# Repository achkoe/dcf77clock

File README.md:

# dcf77clock

DCF77 clock with LED display using Raspberry Pi Pico.

## cc

Software for Raspberry Pi Pico.

## cad

Python files for generating SVG files for different parts
of the case for the clock.

## kicad

KiCAD layout data for clock hardware.

## simulator

Python script to simulate DCF77 sequence on Raspberry Pi.

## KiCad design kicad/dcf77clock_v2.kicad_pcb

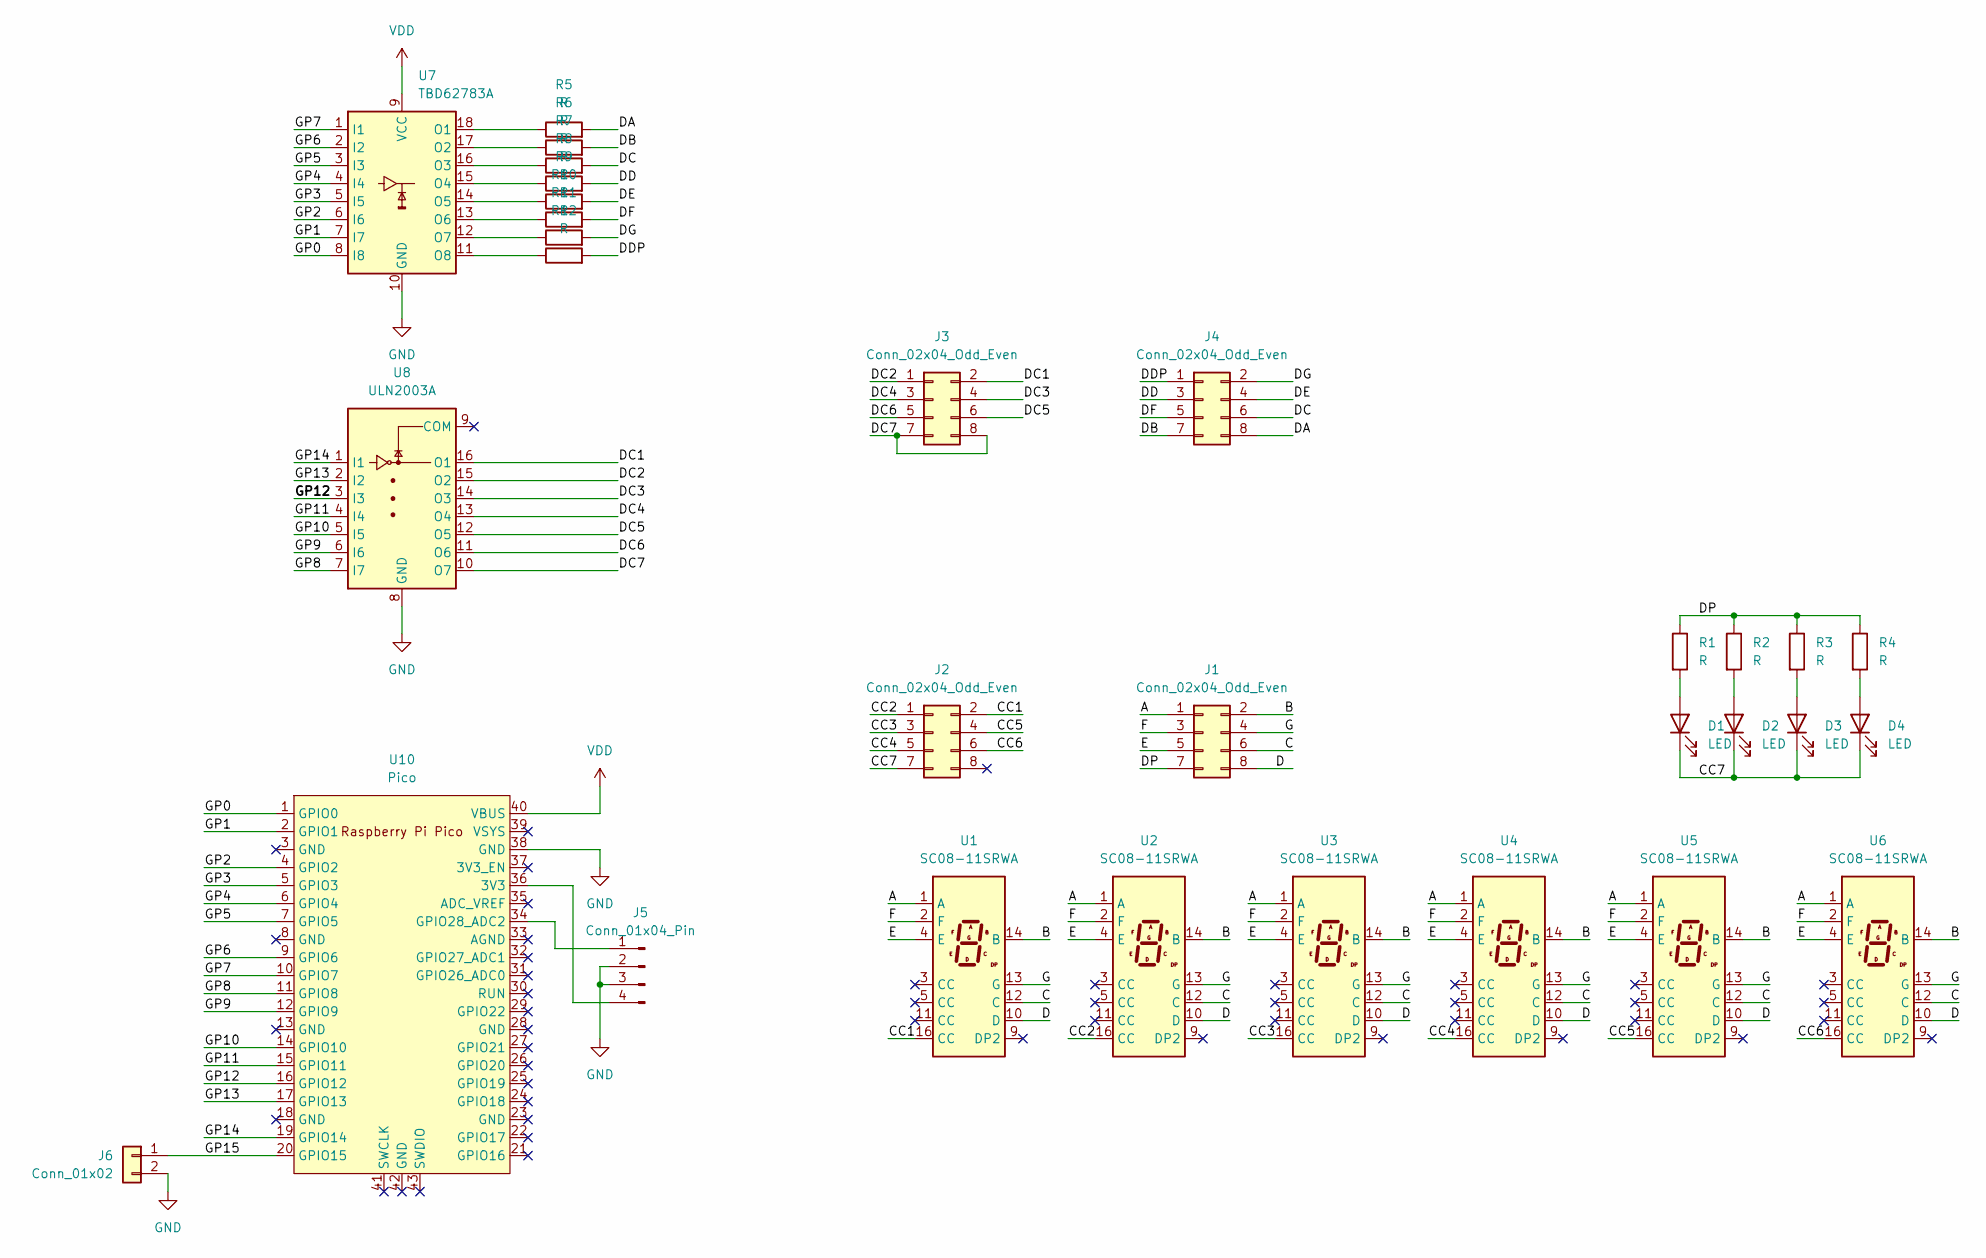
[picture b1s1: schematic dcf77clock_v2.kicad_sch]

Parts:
D1, D2, D3, D4: LED; LED_D3.0mm
J1, J2: Conn_02x04_Odd_Even; PinSocket_2x04_P2.54mm_Vertical
J3, J4: Conn_02x04_Odd_Even; PinHeader_2x04_P2.54mm_Vertical
J5: Conn_01x04_Pin; PinHeader_1x04_P2.54mm_Horizontal
J6: Conn_01x02; PinHeader_1x02_P2.54mm_Horizontal
R1, R2, R3, R4, R5, R6, R7, R8, R9, R10, R11, R12: R; R_Axial_DIN0207_L6.3mm_D2.5mm_P10.16mm_Horizontal
U1, U2, U3, U4, U5, U6: SC08-11SRWA; SC08-11SWRA
U7: TBD62783A; DIP-18_W7.62mm_LongPads
U8: ULN2003A; DIP-16_W7.62mm_LongPads
U10: Pico; RPi_Pico_SMD_TH

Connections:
/A: J1.1, U1.1 (A), U2.1 (A), U3.1 (A), U4.1 (A), U5.1 (A), U6.1 (A)
/B: J1.2, U1.14 (B), U2.14 (B), U3.14 (B), U4.14 (B), U5.14 (B), U6.14 (B)
/C: J1.6, U1.12 (C), U2.12 (C), U3.12 (C), U4.12 (C), U5.12 (C), U6.12 (C)
/CC1: J2.2, U1.16 (CC)
/CC2: J2.1, U2.16 (CC)
/CC3: J2.3, U3.16 (CC)
/CC4: J2.5, U4.16 (CC)
/CC5: J2.4, U5.16 (CC)
/CC6: J2.6, U6.16 (CC)
/CC7: D1.1 (K), D2.1 (K), D3.1 (K), D4.1 (K), J2.7
/D: J1.8, U1.10 (D), U2.10 (D), U3.10 (D), U4.10 (D), U5.10 (D), U6.10 (D)
/DA: J4.8, R5.2
/DB: J4.7, R6.2
/DC: J4.6, R7.2
/DC1: J3.2, U8.16 (O1)
/DC2: J3.1, U8.15 (O2)
/DC3: J3.4, U8.14 (O3)
/DC4: J3.3, U8.13 (O4)
/DC5: J3.6, U8.12 (O5)
/DC6: J3.5, U8.11 (O6)
/DC7: J3.7, J3.8, U8.10 (O7)
/DD: J4.3, R8.2
/DDP: J4.1, R12.2
/DE: J4.4, R9.2
/DF: J4.5, R10.2
/DG: J4.2, R11.2
/DP: J1.7, R1.1, R2.1, R3.1, R4.1
/E: J1.5, U1.4 (E), U2.4 (E), U3.4 (E), U4.4 (E), U5.4 (E), U6.4 (E)
/F: J1.3, U1.2 (F), U2.2 (F), U3.2 (F), U4.2 (F), U5.2 (F), U6.2 (F)
/G: J1.4, U1.13 (G), U2.13 (G), U3.13 (G), U4.13 (G), U5.13 (G), U6.13 (G)
/GP0: U7.8 (I8), U10.1 (GPIO0)
/GP1: U7.7 (I7), U10.2 (GPIO1)
/GP2: U7.6 (I6), U10.4 (GPIO2)
/GP3: U7.5 (I5), U10.5 (GPIO3)
/GP4: U7.4 (I4), U10.6 (GPIO4)
/GP5: U7.3 (I3), U10.7 (GPIO5)
/GP6: U7.2 (I2), U10.9 (GPIO6)
/GP7: U7.1 (I1), U10.10 (GPIO7)
/GP8: U8.7 (I7), U10.11 (GPIO8)
/GP9: U8.6 (I6), U10.12 (GPIO9)
/GP10: U8.5 (I5), U10.14 (GPIO10)
/GP11: U8.4 (I4), U10.15 (GPIO11)
/GP12: U8.3 (I3), U10.16 (GPIO12)
/GP13: U8.2 (I2), U10.17 (GPIO13)
/GP14: U8.1 (I1), U10.19 (GPIO14)
/GP15: J6.1, U10.20 (GPIO15)
GND: J5.2, J5.3, J6.2, U7.10 (GND), U8.8 (GND), U10.38 (GND)
unnamed: D1.2 (A), R1.2
unnamed: D2.2 (A), R2.2
unnamed: D3.2 (A), R3.2
unnamed: D4.2 (A), R4.2
unnamed: J5.1, U10.34 (GPIO28_ADC2)
unnamed: J5.4, U10.36 (3V3)
unnamed: R5.1, U7.18 (O1)
unnamed: R6.1, U7.17 (O2)
unnamed: R7.1, U7.16 (O3)
unnamed: R8.1, U7.15 (O4)
unnamed: R9.1, U7.14 (O5)
unnamed: R10.1, U7.13 (O6)
unnamed: R11.1, U7.12 (O7)
unnamed: R12.1, U7.11 (O8)
VDD: U7.9 (VCC), U10.40 (VBUS)

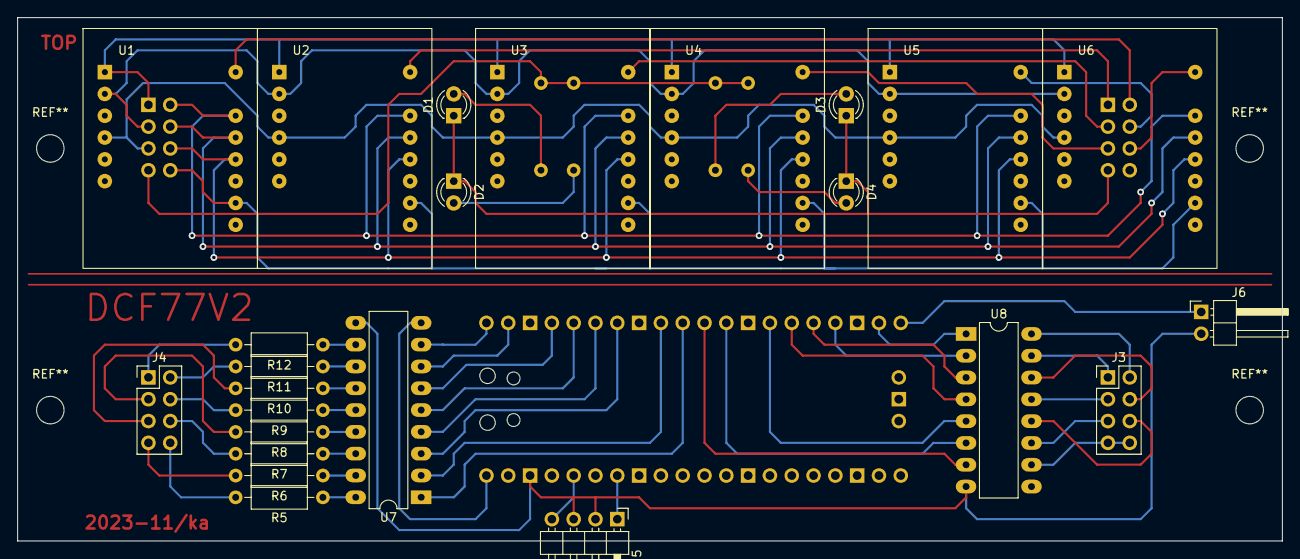
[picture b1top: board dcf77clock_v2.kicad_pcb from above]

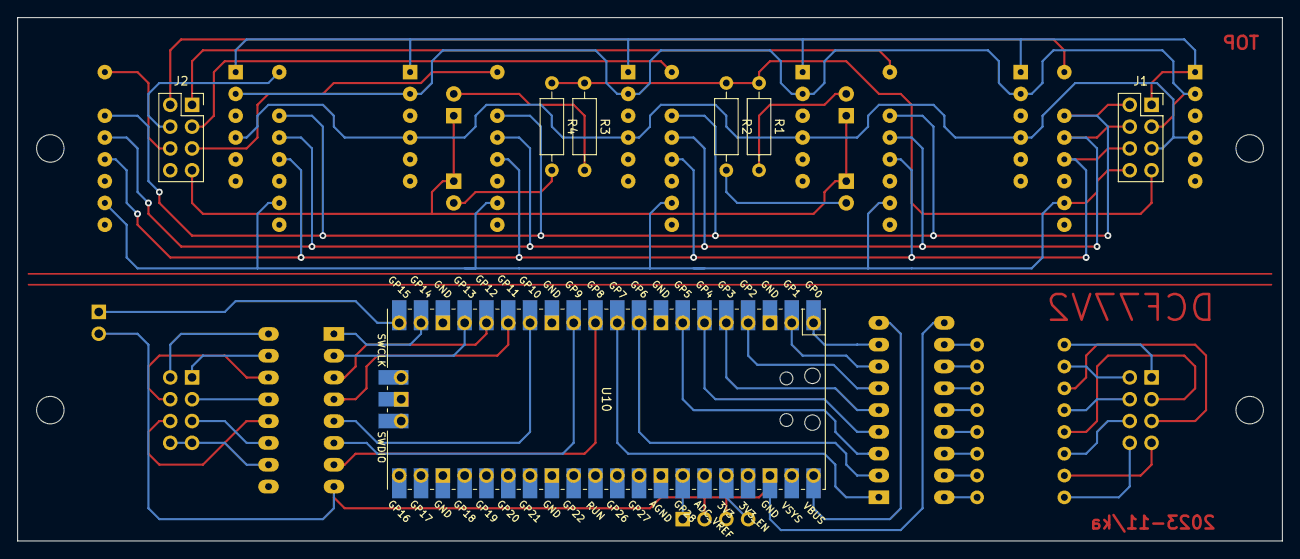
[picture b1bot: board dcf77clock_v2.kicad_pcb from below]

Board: 2 copper layers, 147.3 x 61.0 mm, 31 parts (7 on the bottom side), 62 nets.

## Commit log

2023-12-22 first check in
2023-12-22 added simulator folder, fixed Readme
